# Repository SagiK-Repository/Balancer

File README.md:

문서정보 : 2023.05.26.~ 작성, 작성자 [@SAgiKPJH](https://github.com/SAgiKPJH)  
재개 : 2024.11.30.~ 구성 [@SAgiKPJH](https://github.com/SAgiKPJH) [@ttkpark](https://github.com/ttkpark) [@gypark](https://github.com/gyfolder)

# Balancer
- balancer 만들기

### 회의록
- [x] [2024.11.30](https://github.com/SagiK-Repository/Balancer/issues/1)

### Git Commit 규칙
```
feat: 새로운 기능
fix: 버그 수정 (로직 변경)
refactor: 기능 수정 (코드 변경)
style: 코드 형식
docs: 문서
chore: 기타

merge: 머지 

build: 빌드 관련 내용
test: 테스트
docker: 도커 관련 설정
bug: 버그 개선

ci: ci 관련 내용
cd: cd 관련 내용
cicd: ci/cd관련 내용
```

| 메시지 | 예시 내용 |
| - | - |
| fix | 함수 입/출력이 바뀌는 내용 개선 |
| refactor | 함수 입/출력은 동일하나 알고리즘 개선 |
| style | 함수 기능은 동일하나, 명칭 또는 주석 수정 (+UI 시각적 개선 포함) |
| feature-C | Feature C, Giho Park |
Hello someone

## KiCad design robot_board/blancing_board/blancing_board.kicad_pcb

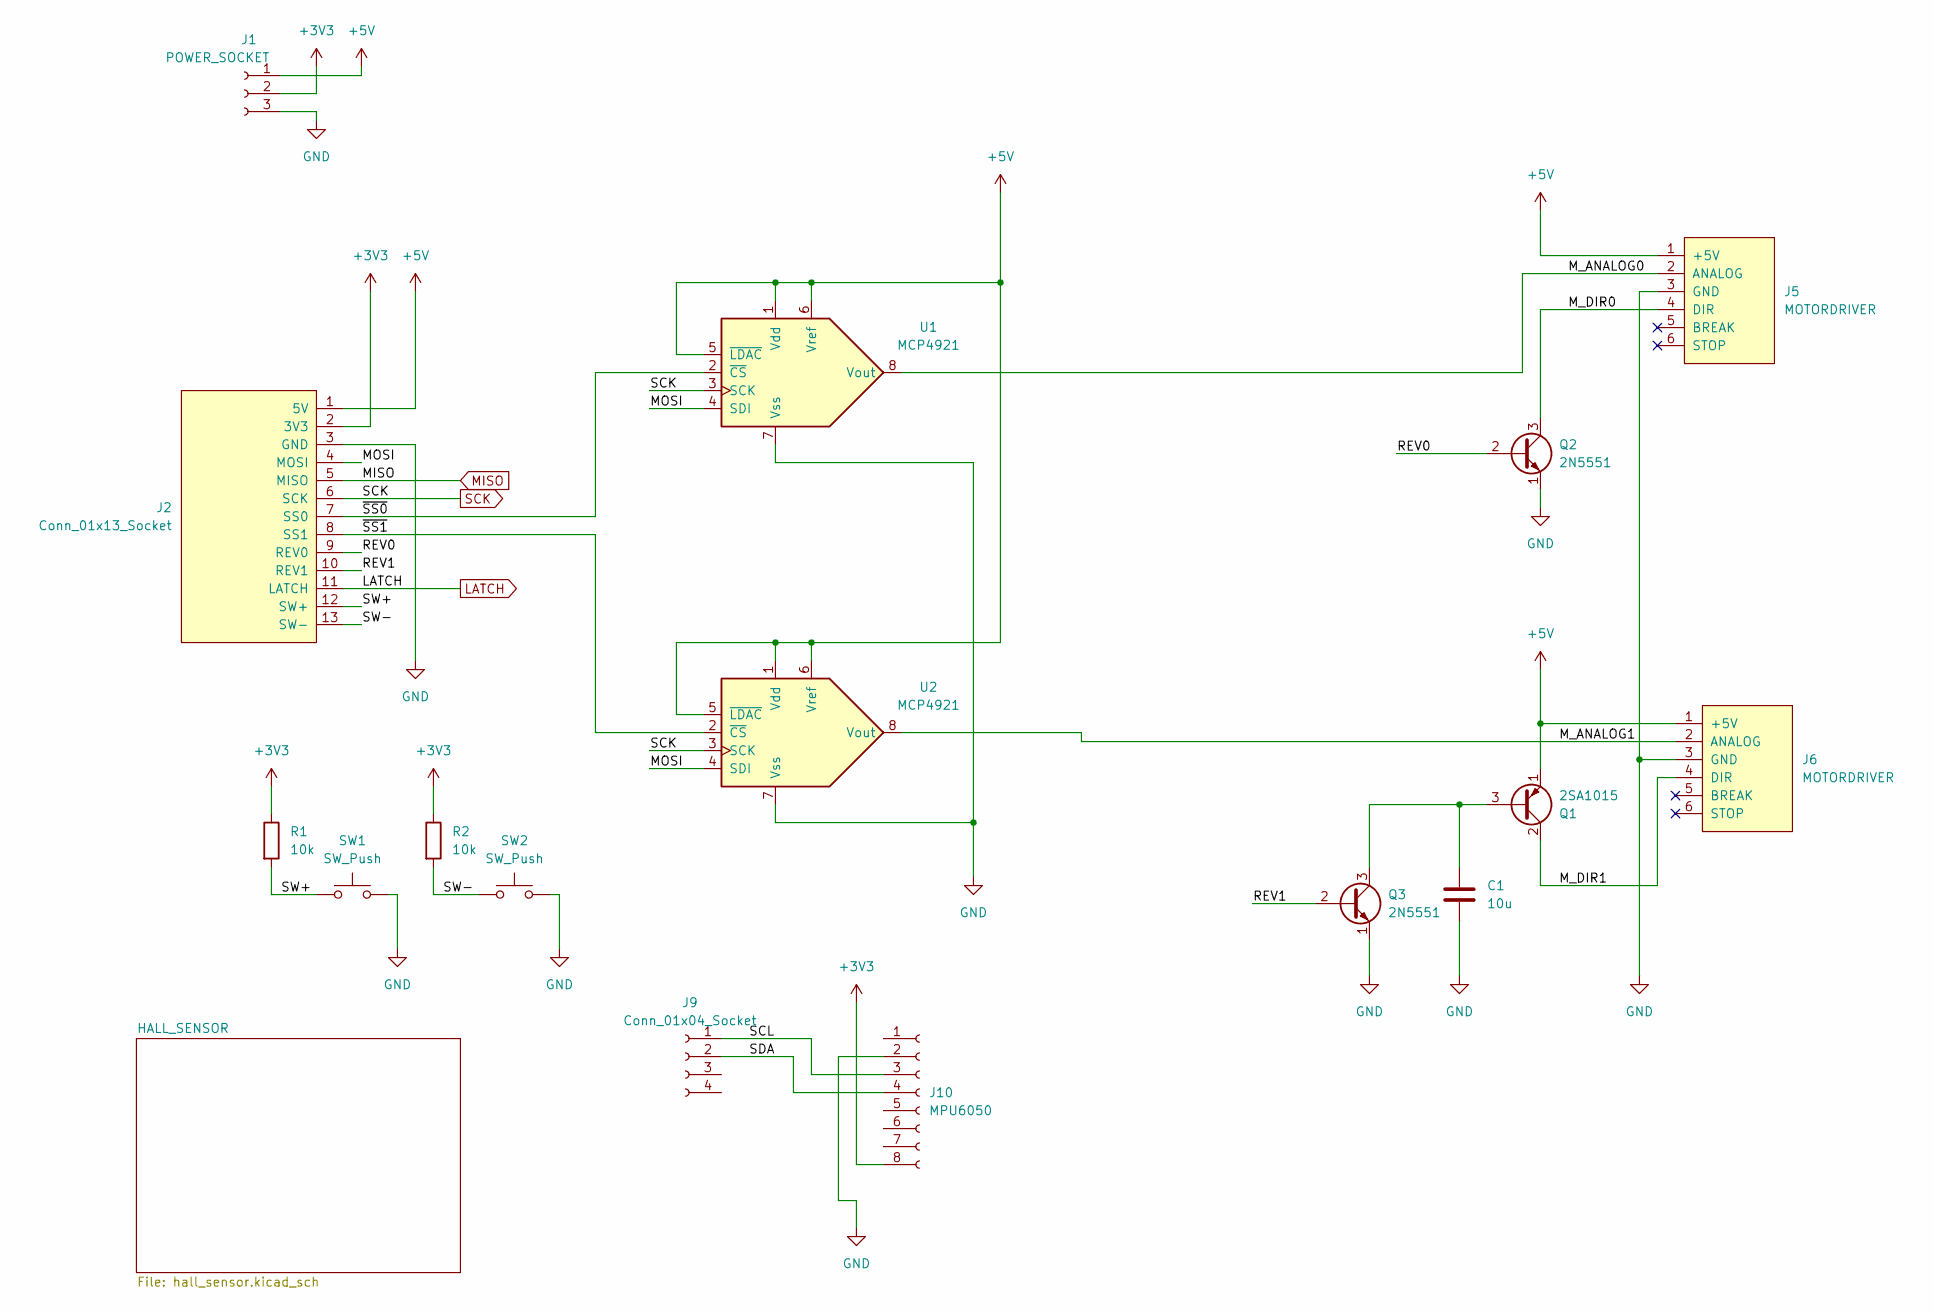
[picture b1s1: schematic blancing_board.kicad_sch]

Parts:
C1: 10u; C_Radial_D6.3mm_H5.0mm_P2.50mm
J1: POWER_SOCKET; TerminalBlock_Phoenix_PT-1,5-3-3.5-H_1x03_P3.50mm_Horizontal
J2: Conn_01x13_Socket; PinHeader_1x13_P2.54mm_Vertical
J5, J6: MOTORDRIVER; PinSocket_1x06_P2.54mm_Vertical
J9: Conn_01x04_Socket; PinHeader_1x04_P2.54mm_Vertical
J10: MPU6050; PinHeader_1x08_P2.54mm_Vertical
Q1: 2SA1015; TO-92_Inline
Q2, Q3: 2N5551; TO-92_Inline
R1, R2: 10k; R_Axial_DIN0207_L6.3mm_D2.5mm_P10.16mm_Horizontal
SW1, SW2: SW_Push; SW_PUSH_6mm
U1, U2: MCP4921; DIP-8_W7.62mm_LongPads

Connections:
+3V3: J1.2, J2.2 (3V3), J10.8, R1.1, R2.1; also elsewhere on the board
+5V: J1.1, J2.1 (5V), J5.1 (+5V), J6.1 (+5V), Q1.1 (E), U1.1 (Vdd), U1.5 (~LDAC), U1.6 (Vref), U2.1 (Vdd), U2.5 (~LDAC), U2.6 (Vref)
/MOSI: J2.4 (MOSI), U1.4 (SDI), U2.4 (SDI)
/M_ANALOG0: J5.2 (ANALOG), U1.8 (Vout)
/M_ANALOG1: J6.2 (ANALOG), U2.8 (Vout)
/M_DIR0: J5.4 (DIR), Q2.3 (C)
/M_DIR1: J6.4 (DIR), Q1.2 (C)
/REV0: J2.9 (REV0), Q2.2 (B)
/REV1: J2.10 (REV1), Q3.2 (B)
/SCL: J9.1, J10.3
/SDA: J9.2, J10.4
/SW+: J2.12 (SW+), R1.2, SW1.1
/SW-: J2.13 (SW-), R2.2, SW2.1
/~SS0: J2.7 (SS0), U1.2 (~CS)
/~SS1: J2.8 (SS1), U2.2 (~CS)
GND: C1.2, J1.3, J2.3 (GND), J5.3 (GND), J6.3 (GND), J10.2, Q2.1 (E), Q3.1 (E), SW1.2, SW2.2, U1.7 (Vss), U2.7 (Vss); also elsewhere on the board
LATCH: J2.11 (LATCH); also elsewhere on the board
MISO: J2.5 (MISO); also elsewhere on the board
unnamed: C1.1, Q1.3 (B), Q3.3 (C)
SCK: J2.6 (SCK), U1.3 (SCK), U2.3 (SCK); also elsewhere on the board

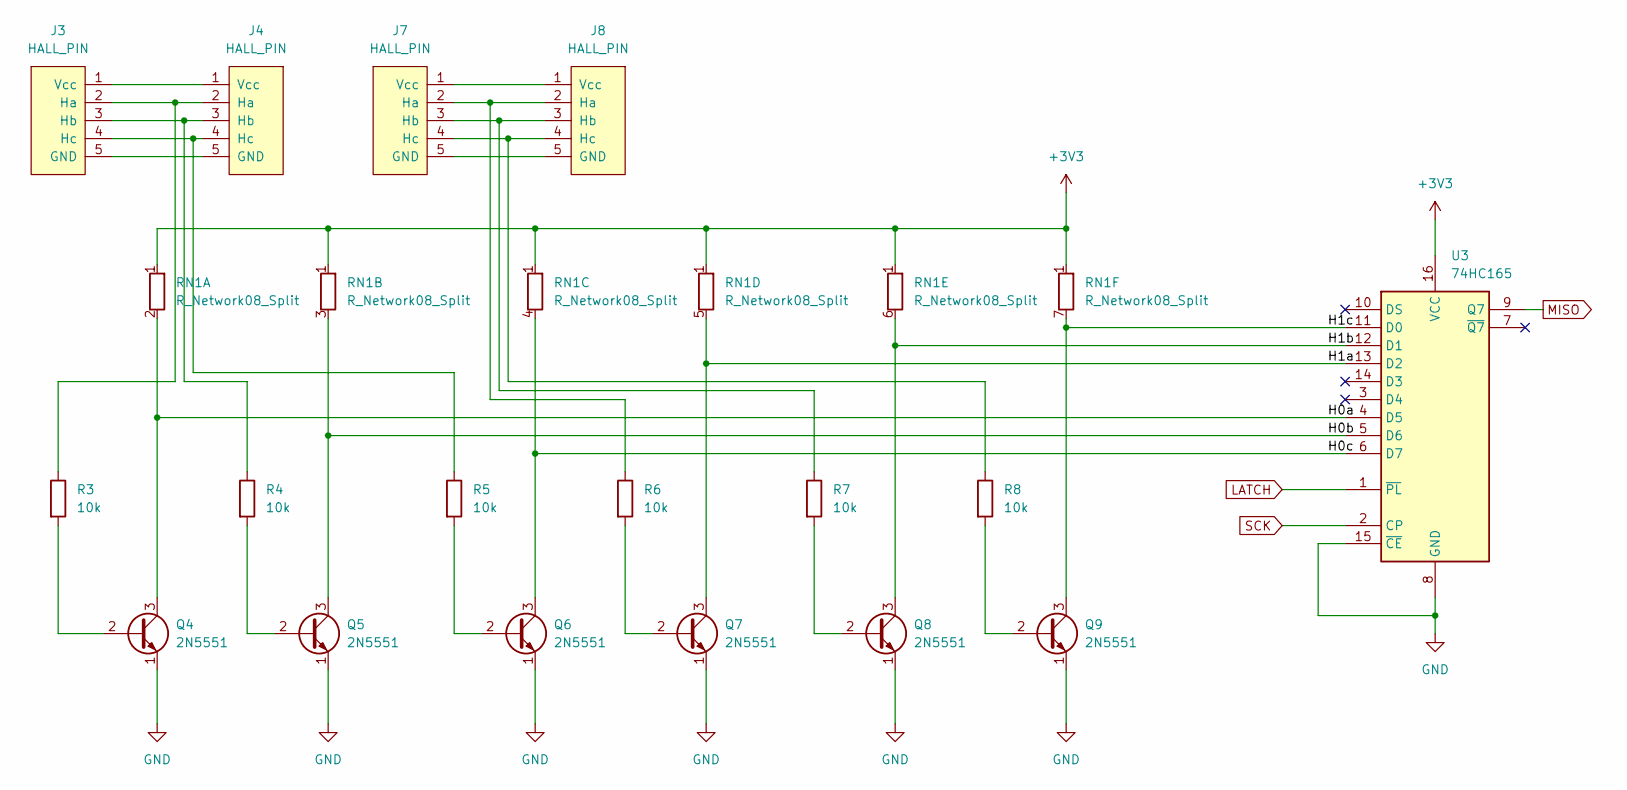
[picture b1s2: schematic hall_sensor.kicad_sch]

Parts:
J3, J4, J7, J8: HALL_PIN; PinHeader_1x05_P2.54mm_Vertical
Q4, Q5, Q6, Q7, Q8, Q9: 2N5551; TO-92_Inline
R3, R4, R5, R6, R7, R8: 10k; R_Axial_DIN0207_L6.3mm_D2.5mm_P10.16mm_Horizontal
RN1: R_Network08_Split; R_Array_SIP9
U3: 74HC165; DIP-16_W7.62mm_LongPads

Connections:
+3V3: RN1.1 (R1), U3.16 (VCC); also elsewhere on the board
/HALL_SENSOR/H0a: Q4.3 (C), RN1.2 (R1.2), U3.4 (D5)
/HALL_SENSOR/H0b: Q5.3 (C), RN1.3 (R2.2), U3.5 (D6)
/HALL_SENSOR/H0c: Q6.3 (C), RN1.4 (R3.2), U3.6 (D7)
/HALL_SENSOR/H1a: Q7.3 (C), RN1.5 (R4.2), U3.13 (D2)
/HALL_SENSOR/H1b: Q8.3 (C), RN1.6 (R5.2), U3.12 (D1)
/HALL_SENSOR/H1c: Q9.3 (C), RN1.7 (R6.2), U3.11 (D0)
GND: Q4.1 (E), Q5.1 (E), Q6.1 (E), Q7.1 (E), Q8.1 (E), Q9.1 (E), U3.8 (GND), U3.15 (~CE); also elsewhere on the board
LATCH: U3.1 (~PL); also elsewhere on the board
MISO: U3.9 (Q7); also elsewhere on the board
unnamed: J3.5 (GND), J4.5 (GND)
unnamed: J3.2 (Ha), J4.2 (Ha), R3.1
unnamed: J3.3 (Hb), J4.3 (Hb), R4.1
unnamed: J3.4 (Hc), J4.4 (Hc), R5.1
unnamed: J3.1 (Vcc), J4.1 (Vcc)
unnamed: J7.5 (GND), J8.5 (GND)
unnamed: J7.2 (Ha), J8.2 (Ha), R6.1
unnamed: J7.3 (Hb), J8.3 (Hb), R7.1
unnamed: J7.4 (Hc), J8.4 (Hc), R8.1
unnamed: J7.1 (Vcc), J8.1 (Vcc)
unnamed: Q4.2 (B), R3.2
unnamed: Q5.2 (B), R4.2
unnamed: Q6.2 (B), R5.2
unnamed: Q7.2 (B), R6.2
unnamed: Q8.2 (B), R7.2
unnamed: Q9.2 (B), R8.2
SCK: U3.2 (CP); also elsewhere on the board

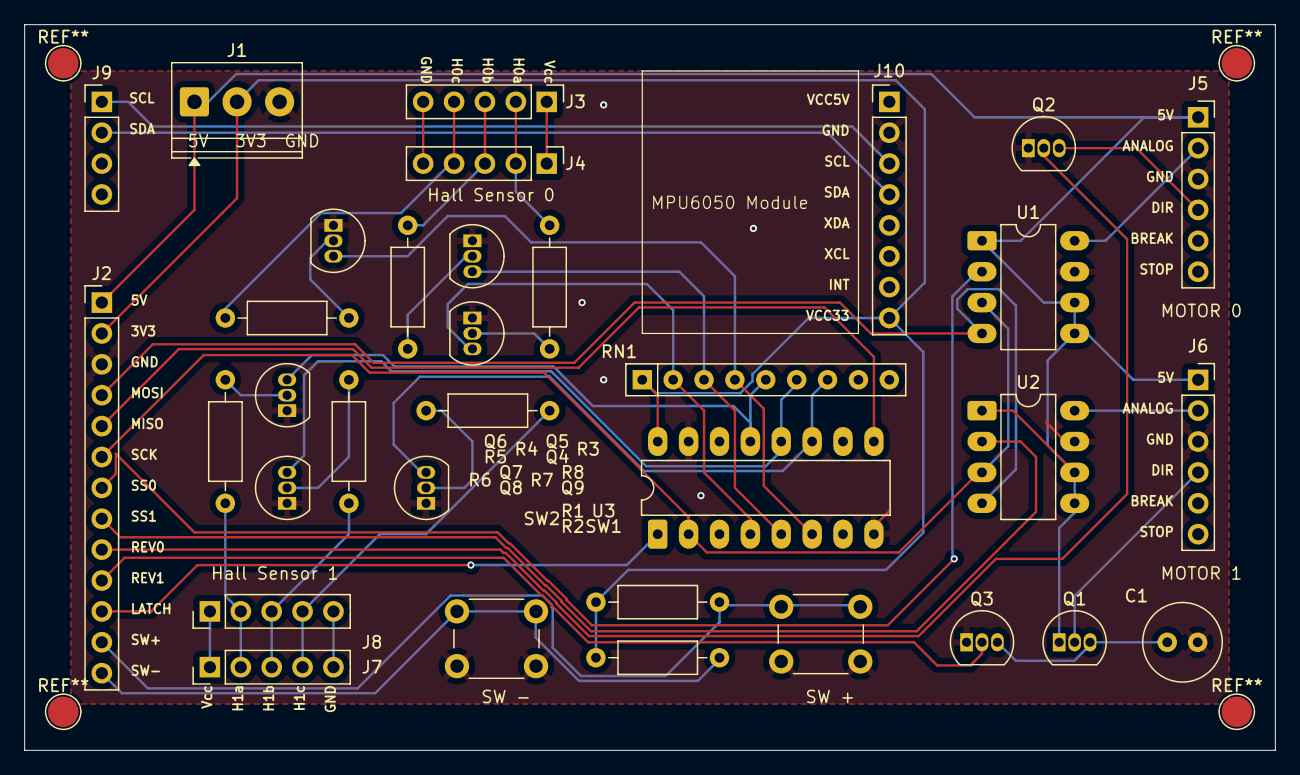
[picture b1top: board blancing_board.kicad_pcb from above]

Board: 2 copper layers, 102.9 x 59.7 mm, 34 parts (0 on the bottom side), 42 nets.

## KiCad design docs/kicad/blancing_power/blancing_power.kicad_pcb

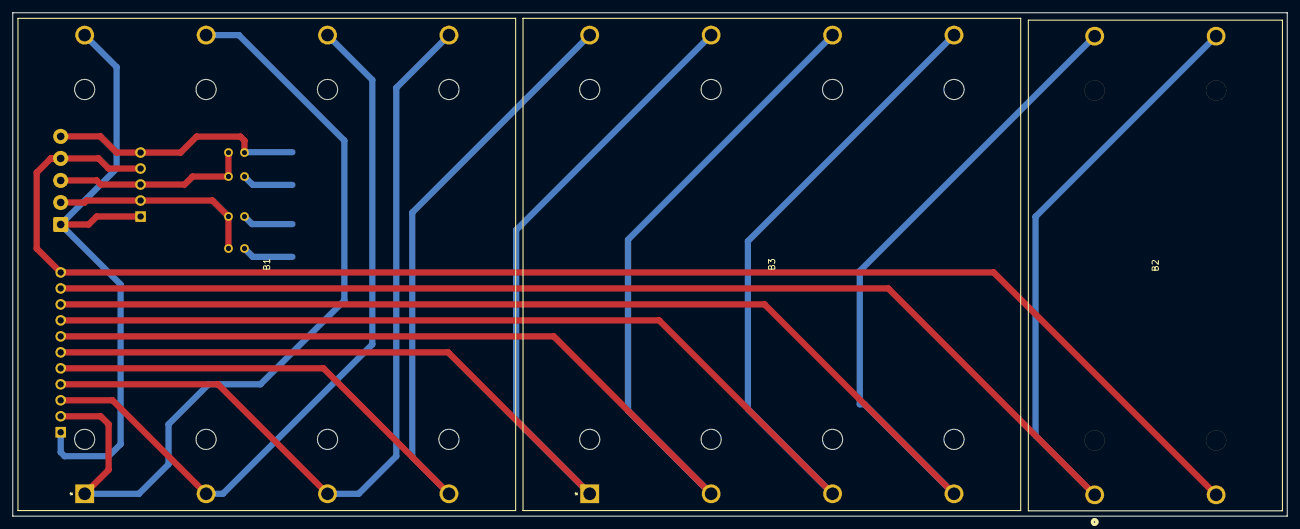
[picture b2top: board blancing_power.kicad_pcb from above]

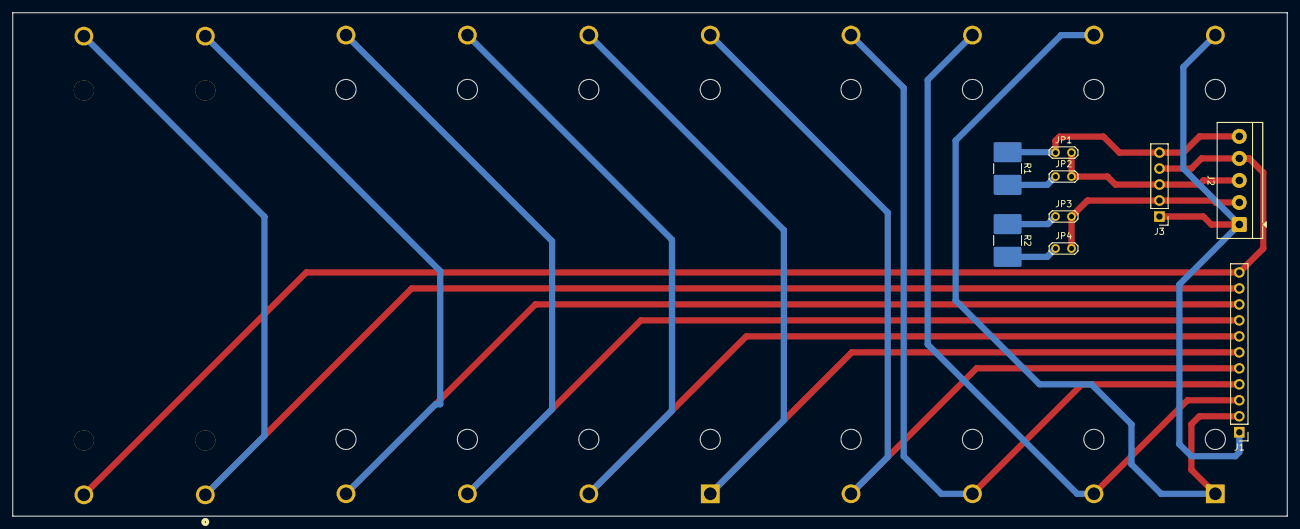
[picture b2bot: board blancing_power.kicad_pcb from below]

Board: 2 copper layers, 202.6 x 80.0 mm, 12 parts (9 on the bottom side), 16 nets.

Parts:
B1, B3: BK-18650-PC8; BK-18650-PC8_MPD
B2: BK-18650-PC4; BK-18650-PC4_MPD
J1: Conn_01x11_Socket; PinHeader_1x11_P2.54mm_Vertical
J2: Conn_01x05_Socket; TerminalBlock_4Ucon_1x05_P3.50mm_Horizontal
J3: Conn_01x05_Socket; PinHeader_1x05_P2.54mm_Vertical
JP1, JP2, JP3, JP4: Jumper_2_Open; TestPoint_2Pads_Pitch2.54mm_Drill0.8mm
R1, R2: R; R_2816_7142Metric_Pad3.20x4.45mm_HandSolder

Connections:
unnamed: B1.1, B1.7, J1.2 (B1)
unnamed: B1.2, B1.6, J1.3 (B2)
unnamed: B1.3, B1.5, J1.4 (B3)
unnamed: B1.4, B3.8, J1.5 (B4)
unnamed: B3.1, B3.7, J1.6 (B5)
unnamed: B3.2, B3.6, J1.7 (B6)
unnamed: B3.3, B3.5, J1.8 (B7)
unnamed: B2.4, B3.4, J1.9 (B8)
unnamed: B2.1, B2.3, J1.10 (B9)
unnamed: B2.2, J1.11 (B+), J2.4 (36V), J3.4
unnamed: B1.8, J1.1 (B-), J2.1 (B-), J3.1
unnamed: J2.2 (C-), J3.2, JP3.2 (B), JP4.2 (B)
unnamed: J2.5 (GND), J3.5, JP1.1 (A), JP3.1 (A), R1.1, R2.1
unnamed: J2.3 (P-), J3.3, JP1.2 (B), JP2.2 (B)
unnamed: JP2.1 (A), R1.2
unnamed: JP4.1 (A), R2.2

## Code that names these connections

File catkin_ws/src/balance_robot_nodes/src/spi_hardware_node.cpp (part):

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    pnh_.param<int>("clk_pin", pin_config_.clk_pin, 18);
    pnh_.param<int>("ss0_pin", pin_config_.ss0_pin, 19);
    pnh_.param<int>("ss1_pin", pin_config_.ss1_pin, 20);
    pnh_.param<int>("latch_pin", pin_config_.latch_pin, 38);
    pnh_.param<int>("reverse0_pin", pin_config_.reverse0_pin, 168);
    pnh_.param<int>("reverse1_pin", pin_config_.reverse1_pin, 13);
    pnh_.param<int>("inc_button_pin", pin_config_.inc_button_pin, 232);
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    ROS_INFO("Loaded GPIO pin configuration:");
    ROS_INFO("  SPI: MOSI=%d, MISO=%d, CLK=%d, SS0=%d, SS1=%d, LATCH=%d", 
             pin_config_.mosi_pin, pin_config_.miso_pin, pin_config_.clk_pin,
             pin_config_.ss0_pin, pin_config_.ss1_pin, pin_config_.latch_pin);
    ROS_INFO("  Motor: REV0=%d, REV1=%d", pin_config_.reverse0_pin, pin_config_.reverse1_pin);
    ROS_INFO("  Button: INC=%d, DEC=%d", pin_config_.inc_button_pin, pin_config_.dec_button_pin);
}

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        ROS_WARN("Failed to initialize reverse1 pin %d - will use dummy mode", pin_config_.reverse1_pin);
        gpio_success = false;
    }
    if (!setOutputLine(pin_config_.latch_pin, &latch_line_)) {
        ROS_WARN("Failed to initialize latch pin %d - will use dummy mode", pin_config_.latch_pin);
        gpio_success = false;
    }
    
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    // 실제 SPI 초기화 시도
    try {
        spi_ = new BitBangSPI(pin_config_.mosi_pin, pin_config_.miso_pin, 
                             pin_config_.clk_pin, pin_config_.latch_pin,
                             BitBangSPI::MODE0, pin_config_.spi_speed, false);
        
        if (!spi_) {
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
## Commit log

2023-05-26 Add Date
2023-05-26 Add 목표
2024-11-30 docs : add 재개 정보, image
2024-11-30 docs : update image
2024-11-30 docs : update readme
2024-11-30 docks : add 회의록
2025-02-02 chore : add gir ignore
2025-02-02 file : add balancing 견적 및 3d model
2025-02-02 Create giho's Note
    giho commit test
2025-02-02 chore : add test
2025-02-02 Rename giho's Note to giho's Note.txt
2025-05-12 0512 commit
2025-05-12 0512
2025-05-13 0513 successsfully connected
2025-05-13 balancing 25.05.13
2025-05-13 additional commit 25.05.13
2025-05-24 250524
2025-05-24 250524 Appended MPU6050 acc sensor & Motor Encoder for Precise displacement and velocity measurement
2025-06-02 20250602 hardware dev
2025-06-04 250604 comment added
2025-06-14 두 바퀴 모터 제어 시스템 구현 - 포괄적인 테스트 노드, 자동화 스크립트, 부드러운 제어 시스템 추가
2025-06-14 new page
2025-06-21 fix: BitBangSPI 클래스 생성자 추가로 컴파일 오류 해결
2025-06-21 feat: 실제 하드웨어 구현으로 노드 업그레이드
    - I2C 센서 노드: 기존 motor_controller의 MPU6050 구현 적용
    * 실제 I2C 통신, 센서 초기화, 보정 기능
    * 가속도계/자이로스코프 데이터 변환 및 필터링
    * 상보 필터를 통한 안정화된 각도 계산
    - SPI 하드웨어 노드: 기존 BitBangSPI, MCP4921, HallSensorEncoder 구현 적용
    * 실제 GPIO 제어를 통한 SPI 통신
2025-06-21 fix: 빌드 오류 수정
    - SPI 객체 타입 불일치 해결: spi_ 멤버를 포인터로 변경
    - HallSensorEncoder 생성자 매개변수 수정: 999 -> 10.0 (max_velocity)
    - HardwareError enum에 I2C_READ_FAILED 추가
    - 생성자 초기화 리스트에 spi_(nullptr) 추가
    모든 빌드 오류가 해결되어 실제 하드웨어 배포 준비 완료
2025-06-21 fix: GPIO 권한 문제 해결 및 motor_controller 호환성 추가
2025-08-27 25.08.27. motor logic pre-activate
2025-08-27 raw angle
2025-08-29 git push
2025-08-29 docs: md파일 image directory 별도 구성
2025-08-29 chore: 불필요한 파일 제거
2025-08-29 chore: dir 구성 변경
2025-08-29 docs: update readme
    add commit rules
2025-08-29 docs: IP주소 변경 시 오류 해결 및 예상 문제 문서 정리
2025-08-29 docs : image delete
    delete unused image
2025-08-29 docs: IP주소 바뀔때 대처법 위치 이동
2025-08-29 docs: patch-rules 설정
2025-08-29 docs: update readme
2025-08-29 docs: project feature C modified
2025-08-29 docs: remove readme
2025-08-29 docs: edit README
2025-08-30 feat: balance logic edit
2025-08-30 refactor: 밸런싱 PID 변경
2025-08-30 refactor: 밸런싱 1차 튜닝 완료
2025-08-30 docs: 밸런싱 첫 안정화 문서 수정
2025-12-04 홀 센서 비트 파싱 수정: Motor0과 Motor1 모두 2비트 사용 (bit 2-3, bit 6-7)
2025-12-04 SSH 원격 프로젝트 업로드 및 빌드 가이드 문서 추가
2025-12-04 feat: 딜레이 감소를 위한 버전 2 ROS 빌드 프로젝트 생성 및 하드웨어 테스트
